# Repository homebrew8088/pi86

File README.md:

# pi86

\
\
This is the code for my 8088/8086 (Really V20/V30) Raspberry Pi "hat"

https://www.homebrew8088.com/home/raspberry-pi-second-project

The code is fairly simple and easy to modify. Basically the Raspberry PI toggles the Clock then reads the Control Bus and then provides the 8088 what it is requesting. It will read the ALE pin and save the address then provide the proper Memory or IO Read/Write.  

Disadvantages:  

The speed, the processor is only running at about 0.3 MHz the best I could calculate.  But on the flip side the drive read writes are very fast because the memory is virtual on raspberry pi.

Not all 8088/8086 Processors will work. The power is connected to the 3.3v pin on the PI. Most NEC V20/V30's will operate 3V - 7V so this is not problem.   

I have written a c library that helps with interfacing the 8088 PCB.  I have also begun to develop a GUI window that emulates CGA/VGA graphics 

**I tested this with a fresh install of Raspberry PI os and it ran just fine.**

Open Terminal

git clone https://github.com/homebrew8088/pi86.git

sudo apt-get update    

sudo apt-get upgrade

sudo apt-get install gcc build-essential libsdl2-dev

sudo apt-get install nasm

git clone https://github.com/WiringPi/WiringPi.git

cd WiringPi

git pull origin

./build

cd ..

cd pi86

cd v20 (or v30)

sudo chmod +x pi86  (or pi86.)

./pi86

*** This is experimental use at your own risk. 

This current build runs very stable. I have left it running for seveal hours and came back and it was still running just fine. I encourage you to download the source code to the projects and give them a try and make modification.

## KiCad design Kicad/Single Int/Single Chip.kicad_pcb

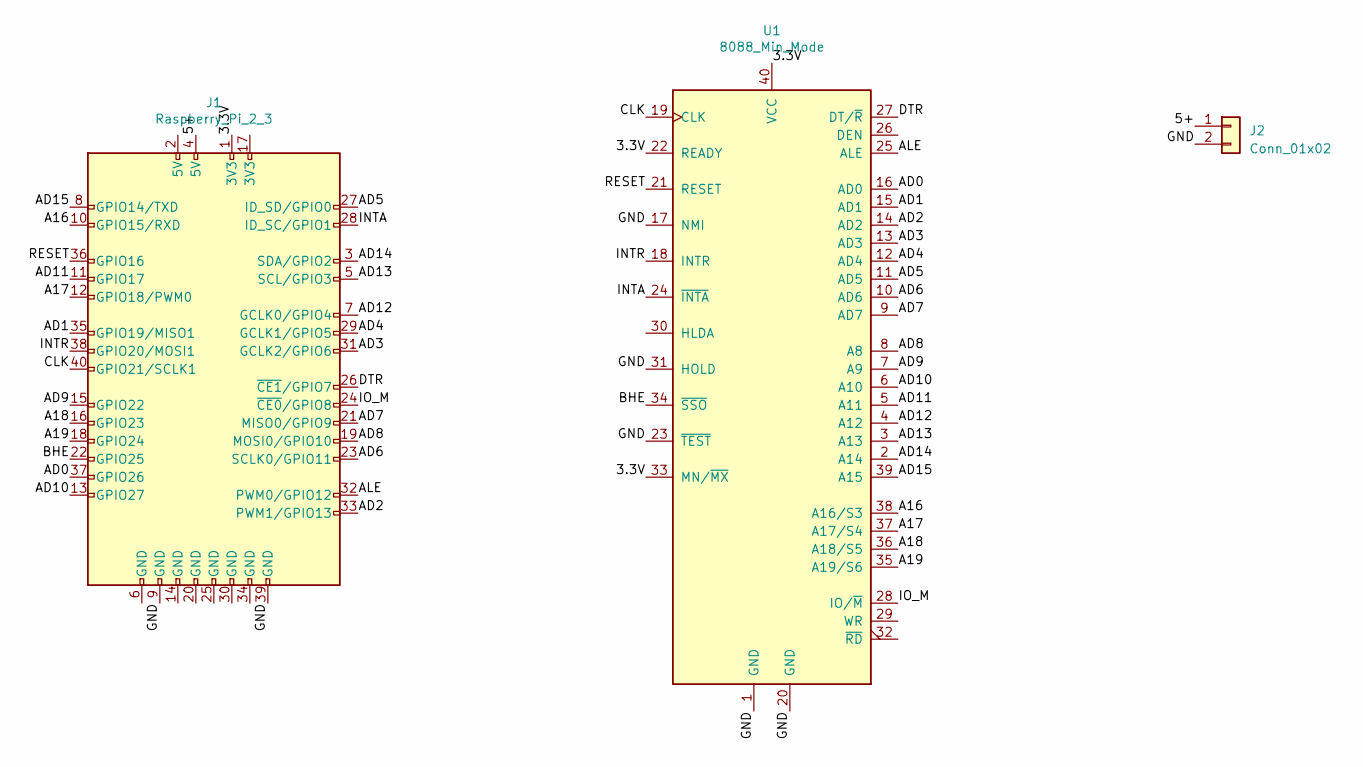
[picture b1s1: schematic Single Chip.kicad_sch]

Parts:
J1: Raspberry_Pi_2_3; PinHeader_2x20_P2.54mm_Vertical
J2: Conn_01x02; PinHeader_1x02_P2.54mm_Vertical
U1: 8088_Min_Mode; DIP-40_W15.24mm

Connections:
/3.3V: J1.1 (3V3), U1.22 (READY), U1.33 (MN/~MX), U1.40 (VCC)
/5+: J1.4 (5V), J2.1
/A16: J1.10 (GPIO15/RXD), U1.38 (A16/S3)
/A17: J1.12 (GPIO18/PWM0), U1.37 (A17/S4)
/A18: J1.16 (GPIO23), U1.36 (A18/S5)
/A19: J1.18 (GPIO24), U1.35 (A19/S6)
/AD0: J1.37 (GPIO26), U1.16 (AD0)
/AD1: J1.35 (GPIO19/MISO1), U1.15 (AD1)
/AD2: J1.33 (PWM1/GPIO13), U1.14 (AD2)
/AD3: J1.31 (GCLK2/GPIO6), U1.13 (AD3)
/AD4: J1.29 (GCLK1/GPIO5), U1.12 (AD4)
/AD5: J1.27 (ID_SD/GPIO0), U1.11 (AD5)
/AD6: J1.23 (SCLK0/GPIO11), U1.10 (AD6)
/AD7: J1.21 (MISO0/GPIO9), U1.9 (AD7)
/AD8: J1.19 (MOSI0/GPIO10), U1.8 (A8)
/AD9: J1.15 (GPIO22), U1.7 (A9)
/AD10: J1.13 (GPIO27), U1.6 (A10)
/AD11: J1.11 (GPIO17), U1.5 (A11)
/AD12: J1.7 (GCLK0/GPIO4), U1.4 (A12)
/AD13: J1.5 (SCL/GPIO3), U1.3 (A13)
/AD14: J1.3 (SDA/GPIO2), U1.2 (A14)
/AD15: J1.8 (GPIO14/TXD), U1.39 (A15)
/ALE: J1.32 (PWM0/GPIO12), U1.25 (ALE)
/BHE: J1.22 (GPIO25), U1.34 (~SSO)
/CLK: J1.40 (GPIO21/SCLK1), U1.19 (CLK)
/DTR: J1.26 (~CE1/GPIO7), U1.27 (DT/~R)
/GND: J1.9 (GND), J1.39 (GND), J2.2, U1.1 (GND), U1.17 (NMI), U1.20 (GND), U1.23 (~TEST), U1.31 (HOLD)
/INTA: J1.28 (ID_SC/GPIO1), U1.24 (~INTA)
/INTR: J1.38 (GPIO20/MOSI1), U1.18 (INTR)
/IO_M: J1.24 (~CE0/GPIO8), U1.28 (IO/~M)
/RESET: J1.36 (GPIO16), U1.21 (RESET)

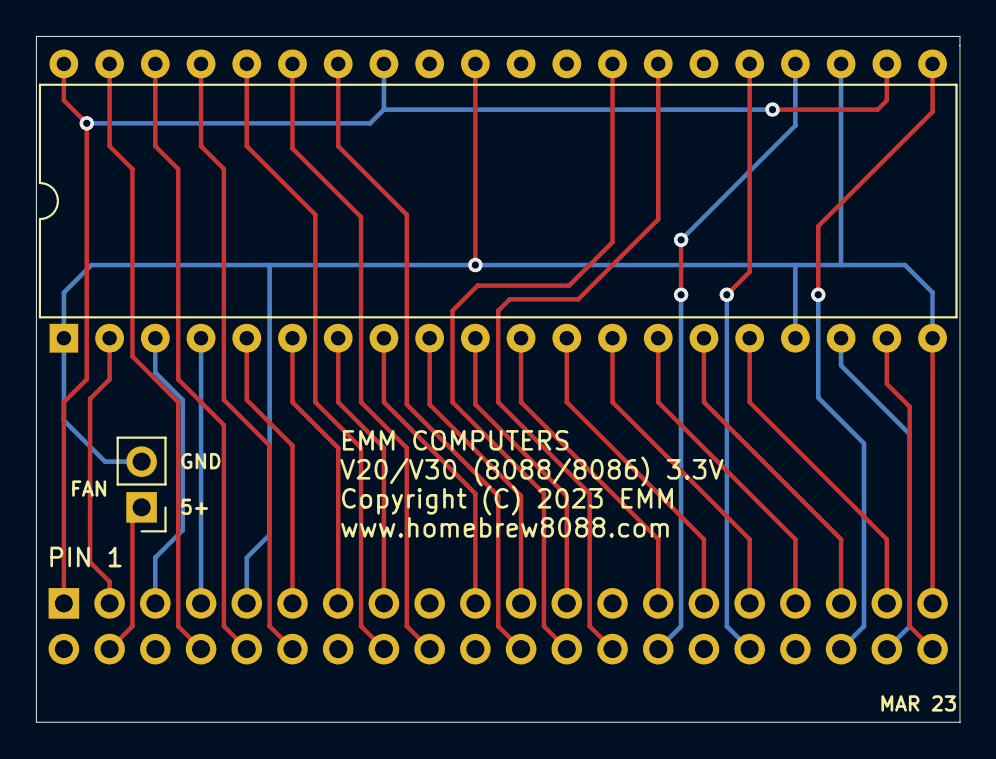
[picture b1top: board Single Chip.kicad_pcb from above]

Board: 2 copper layers, 51.3 x 38.1 mm, 3 parts (1 on the bottom side), 31 nets.

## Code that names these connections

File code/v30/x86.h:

#ifndef X86_H
#define X86_H

#define V20 	88
#define V30 	86 

#define PIN_CLK   29
#define PIN_RESET 27
#define PIN_ALE   26
#define PIN_IO_M  10
#define PIN_DTR   11
#define PIN_BHE   6

#define PIN_INTR  28
#define PIN_INTA  31

#define AD0   25
#define AD1   24
#define AD2   23
#define AD3   22
#define AD4   21
#define AD5   30
#define AD6   14
#define AD7   13

#define A8    12
#define A9    3
#define A10   2
#define A11   0
#define A12   7
#define A13   9
#define A14   8
#define A15   15

#define A16   16
#define A17   1
#define A18   4 
#define A19   5

#include <wiringPi.h>
#include <string>
#include <thread>
#include <unistd.h>
#include <fstream> 

using namespace std;

static bool Stop_Flag;


void Reset();	
void Start(int Processor);
void Load_Bios(string Bios_file);
//Memory
void Write_Memory_Array(unsigned long long int Address, char code_for_8088[], int Length);
void Read_Memory_Array(unsigned long long int Address, char* char_Array, int Length);
void Write_Memory_Byte(unsigned long long int Address, char byte_for_8088);
char Read_Memory_Byte(unsigned long long int Address);		
void Write_Memory_Word(unsigned long long int Address, unsigned short int word_for_8088);
//IO

void Write_IO_Byte(unsigned long long int Address, char byte_for_8088);
char Read_IO_Byte(unsigned long long int Address);
void Write_IO_Word(unsigned long long int Address, unsigned short int word_for_8088);

//INT

void IRQ0();
void IRQ1();
#endif

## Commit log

2021-11-08 initial upload
2021-11-12 Added image to README.md
2022-07-20 Added Kicad files
2023-02-14 Update PCB
2023-02-14 Fixed Schematic and PCB
2023-02-21 Gerber
2023-04-16 add io array functions x86
2023-04-16 small fix
2023-04-16 Fix stop byte
2023-04-16 Mem Array fix
2023-04-16 Updated BIOS
2023-04-16 fixing scan codes
2023-04-16 working on scan codes
2023-04-16 working scan codes
2023-04-16 covert v30 code
2023-04-16 more work
2023-04-16 working color
2023-04-16 Transfer back
2023-05-27 switched back to socket
2023-07-20 added CMakeLists.txt for convenient compiling

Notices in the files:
Kicad/Single Int/Single Chip.kicad_pcb:
Copyright (C) 2023 EMM
